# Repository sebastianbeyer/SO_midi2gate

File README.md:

Simple Midi to gate module with 12 gates. It's in the
[KOSMO format](https://www.lookmumnocomputer.com/modular)
made by Look Mum No Computer (20cm high, 7.5cm wide). Gates are 5V.

## How to get it

Download the [lates release](https://github.com/sebastianbeyer/SO_midi2gate/releases/latest)
including the gerber files and Arduino code

## Arduino code

The code can be found in the code directory and requires only a
[midi library](https://github.com/FortySevenEffects/arduino_midi_library).
Install instructions for this lib can be found
[in the repo](https://github.com/FortySevenEffects/arduino_midi_library#getting-started).

## Schematic

## BOM

| Reference| Quantity | Value | Description |
| -------- | -------- | ----- | ----------- |
| A1  | 1 |  Arduino Nano | |
| C1, C2, C5 |        3 | 10u   | EL cap      |
| C3, C4, C6, C7, C8, C9, C10, C11 | 8 |100n | ceramic disc cap |
| D1 | 1 | 1N4148 | diode |
| D2, D3, D4, D5, D6, D7, D8, D9, D10, D11, D12, D13 | 12 | LED | legs should be
25mm long|
| J1, J2 | 2 | MIDI jacks | |
| J1, J2 | 2 | Molex 3pin  | for MIDI jacks, you can also solder directly |
| J3, ... J15 |12 | Large jack sockets | |
| R1, R13, R14 | 3 | 220 | |
| R2, R3 | 2 | 10R | |
| R4, R5, R6, R7, R8, R9, R10, R11, R15, R16, R17, R18, R19, R20, R21, R22, R23, R24, R25, R26, R27, R28, R29, R30 | 24 |1k | |
| R12 | 1 | 10k |  |
| U1, U4, U5 | 3 | TL074 | opamp |
| U2 | 1 | 6N137 | optocoupler for midi |
| U3 | 1 | L7805 | 5V regulator |

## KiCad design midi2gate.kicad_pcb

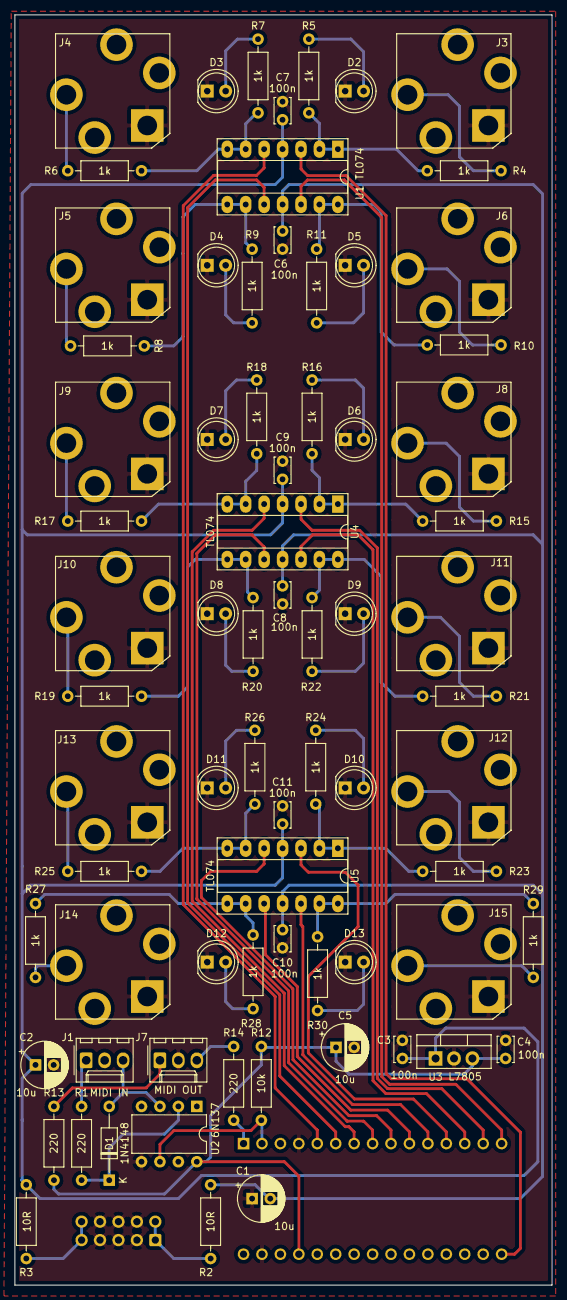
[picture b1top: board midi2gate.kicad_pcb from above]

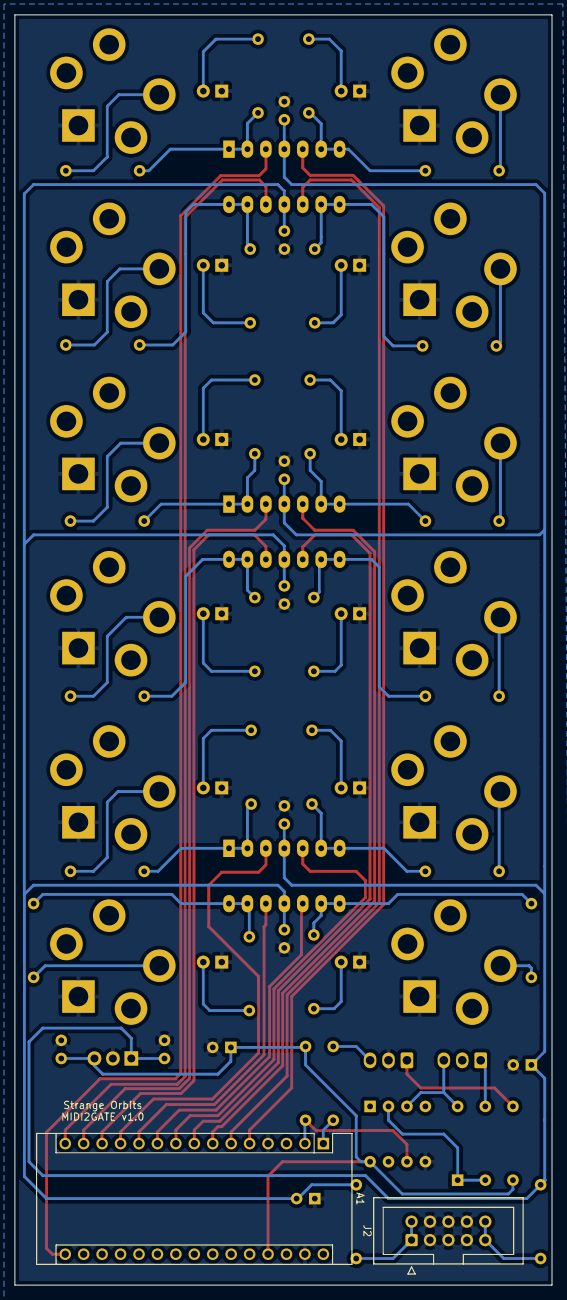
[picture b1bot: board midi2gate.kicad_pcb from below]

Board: 2 copper layers, 74.0 x 175.0 mm, 75 parts (2 on the bottom side), 61 nets.

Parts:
A1: Arduino_Nano_v3.x; Arduino_Nano
C1, C2, C5: 10u; CP_Radial_D6.3mm_P2.50mm
C3, C4, C6, C7, C8, C9, C10, C11: 100n; C_Disc_D3.4mm_W2.1mm_P2.50mm
D1: 1N4148; D_DO-35_SOD27_P10.16mm_Horizontal
D2, D3, D4, D5, D6, D7, D8, D9, D10, D11, D12, D13: LED; LED_D5.0mm
J1: MIDI IN; Molex_KK-254_AE-6410-03A_1x03_P2.54mm_Vertical
J2: Eurorack power; IDC-Header_2x05_P2.54mm_Vertical
J3: GATE1; Jack_6.35mm_PJ_629HAN
J4: GATE2; Jack_6.35mm_PJ_629HAN
J5: GATE3; Jack_6.35mm_PJ_629HAN
J6: GATE4; Jack_6.35mm_PJ_629HAN
J7: MIDI OUT; Molex_KK-254_AE-6410-03A_1x03_P2.54mm_Vertical
J8: GATE5; Jack_6.35mm_PJ_629HAN
J9: GATE6; Jack_6.35mm_PJ_629HAN
J10: GATE7; Jack_6.35mm_PJ_629HAN
J11: GATE8; Jack_6.35mm_PJ_629HAN
J12: GATE9; Jack_6.35mm_PJ_629HAN
J13: GATE10; Jack_6.35mm_PJ_629HAN
J14: GATE11; Jack_6.35mm_PJ_629HAN
J15: GATE12; Jack_6.35mm_PJ_629HAN
R1, R13, R14: 220; R_Axial_DIN0207_L6.3mm_D2.5mm_P7.62mm_Horizontal_silkvalue
R2, R3: 10R; R_Axial_DIN0207_L6.3mm_D2.5mm_P7.62mm_Horizontal_silkvalue
R4, R5, R6, R7, R8, R9, R10, R11, R15, R16, R17, R18, R19, R20, R21, R22, R23, R24, R25, R26, R27, R28, R29, R30: 1k; R_Axial_DIN0207_L6.3mm_D2.5mm_P7.62mm_Horizontal_silkvalue
R12: 10k; R_Axial_DIN0207_L6.3mm_D2.5mm_P7.62mm_Horizontal_silkvalue
U1, U4, U5: TL074; DIP-14_W7.62mm_Socket_LongPads
U2: 6N137; DIP-8_W7.62mm
U3: L7805; TO-220-3_Vertical

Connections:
+5V: A1.27, C4.1, C5.1, R12.1, R13.1, U2.8, U3.3
+12V: C2.1, C3.1, C7.2, C9.2, C11.2, R3.2, U1.4, U3.1, U4.4, U5.4
-12V: C1.2, C6.2, C8.2, C10.2, R2.2, U1.11, U4.11, U5.11
G1: A1.16, U1.3
G2: A1.5, U1.5
G3: A1.6, U1.10
G4: A1.15, U1.12
G5: A1.14, U4.3
G6: A1.7, U4.5
G7: A1.8, U4.10
G8: A1.13, U4.12
G9: A1.12, U5.3
G10: A1.9, U5.5
G11: A1.10, U5.10
G12: A1.11, U5.12
GND: A1.4, A1.29, C1.1, C2.2, C3.2, C4.2, C5.2, C6.1, C7.1, C8.1, C9.1, C10.1, C11.1, D2.1, D3.1, D4.1, D5.1, D6.1, D7.1, D8.1, D9.1, D10.1, D11.1, D12.1, D13.1, J2.3, J2.4, J2.5, J2.6, J2.7, J2.8, J3.S, J4.S, J5.S, J6.S, J7.2, J8.S, J9.S, J10.S, J11.S, J12.S, J13.S, J14.S, J15.S, U2.5, U3.2
MIDI_IN: A1.2, R12.2, U2.6
MIDI_OUT: A1.1, R14.1
unnamed: D1.1, R1.2, U2.2
unnamed: D1.2, J1.3, U2.3
unnamed: D2.2, R5.2
unnamed: D3.2, R7.2
unnamed: D4.2, R9.2
unnamed: D5.2, R11.2
unnamed: D6.2, R16.2
unnamed: D7.2, R18.2
unnamed: D8.2, R20.2
unnamed: D9.2, R22.2
unnamed: D10.2, R24.2
unnamed: D11.2, R26.2
unnamed: D12.2, R28.2
unnamed: D13.2, R30.2
unnamed: J1.1, R1.1
unnamed: J2.1, J2.2, R2.1
unnamed: J2.9, J2.10, R3.1
unnamed: J3.T, R4.2
unnamed: J4.T, R6.2
unnamed: J5.T, R8.2
unnamed: J6.T, R10.2
unnamed: J7.1, R13.2
unnamed: J7.3, R14.2
unnamed: J8.T, R15.2
unnamed: J9.T, R17.2
unnamed: J10.T, R19.2
unnamed: J11.T, R21.2
unnamed: J12.T, R23.2
unnamed: J13.T, R25.2
unnamed: J14.T, R27.2
unnamed: J15.T, R29.2
unnamed: R4.1, R5.1, U1.1, U1.2
unnamed: R6.1, R7.1, U1.6, U1.7
unnamed: R8.1, R9.1, U1.8, U1.9
unnamed: R10.1, R11.1, U1.13, U1.14
unnamed: R15.1, R16.1, U4.1, U4.2
unnamed: R17.1, R18.1, U4.6, U4.7
unnamed: R19.1, R20.1, U4.8, U4.9
unnamed: R21.1, R22.1, U4.13, U4.14
unnamed: R23.1, R24.1, U5.1, U5.2
unnamed: R25.1, R26.1, U5.6, U5.7
unnamed: R27.1, R28.1, U5.8, U5.9
unnamed: R29.1, R30.1, U5.13, U5.14

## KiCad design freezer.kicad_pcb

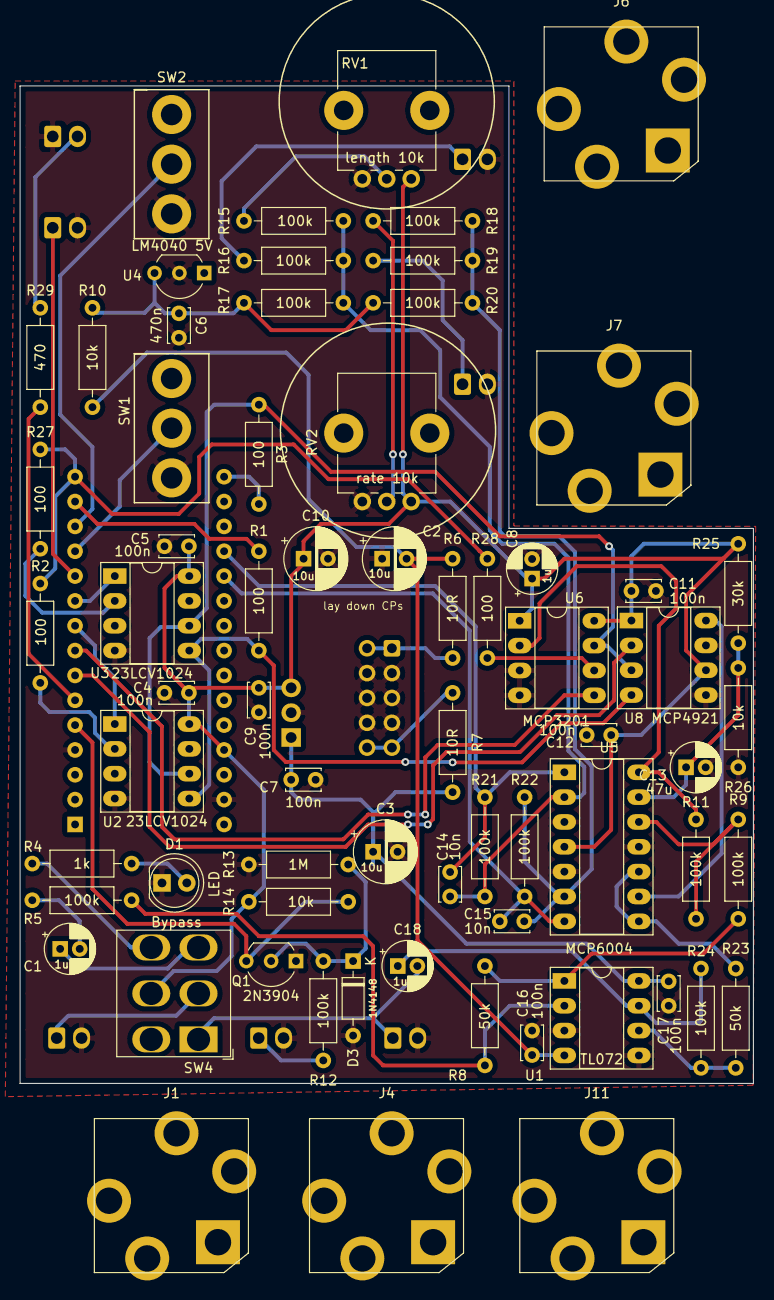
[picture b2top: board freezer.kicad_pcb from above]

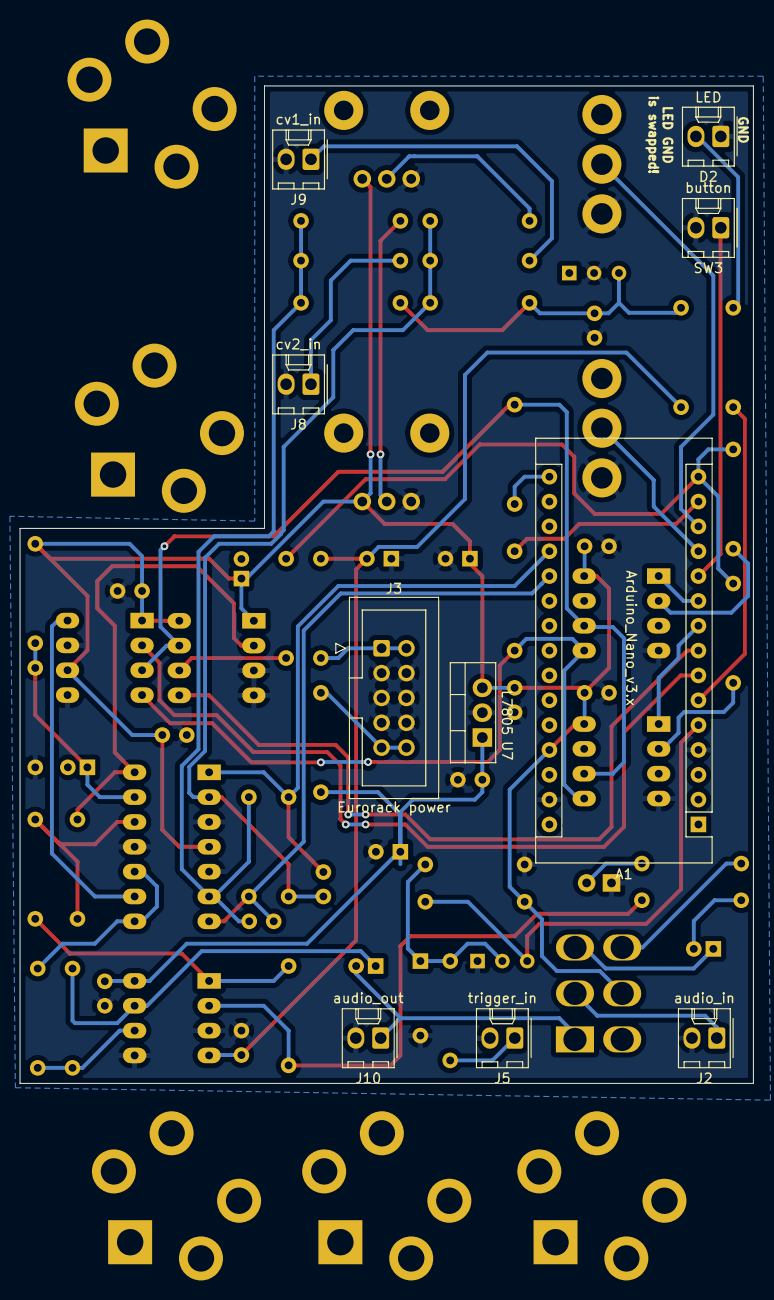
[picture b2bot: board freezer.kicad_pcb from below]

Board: 2 copper layers, 75.0 x 102.0 mm, 77 parts (10 on the bottom side), 50 nets.

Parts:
A1: Arduino_Nano_v3.x; Arduino_Nano
C1, C8, C18: 1u; CP_Radial_D5.0mm_P2.00mm
C2, C3, C10: 10u; CP_Radial_D6.3mm_P2.50mm
C4, C5, C7, C9, C11, C12, C16, C17: 100n; C_Disc_D3.4mm_W2.1mm_P2.50mm
C6: 470n; C_Disc_D3.4mm_W2.1mm_P2.50mm
C13: 47u; CP_Radial_D5.0mm_P2.00mm
C14, C15: 10n; C_Disc_D3.4mm_W2.1mm_P2.50mm
D1: LED; LED_D5.0mm
D2: LED; Molex_KK-254_AE-6410-02A_1x02_P2.54mm_Vertical
D3: 1N4148; D_DO-35_SOD27_P7.62mm_Horizontal
J1: audio in; Jack_6.35mm_PJ_629HAN
J2: audio_in; Molex_KK-254_AE-6410-02A_1x02_P2.54mm_Vertical
J3: Eurorack power; IDC-Header_2x05_P2.54mm_Vertical
J4: trigger in; Jack_6.35mm_PJ_629HAN
J5: trigger_in; Molex_KK-254_AE-6410-02A_1x02_P2.54mm_Vertical
J6: CV1 in; Jack_6.35mm_PJ_629HAN
J7: CV2 in; Jack_6.35mm_PJ_629HAN
J8: cv2_in; Molex_KK-254_AE-6410-02A_1x02_P2.54mm_Vertical
J9: cv1_in; Molex_KK-254_AE-6410-02A_1x02_P2.54mm_Vertical
J10: audio_out; Molex_KK-254_AE-6410-02A_1x02_P2.54mm_Vertical
J11: audio out; Jack_6.35mm_PJ_629HAN
Q1: 2N3904; TO-92_Inline_Wide
R1, R2, R3, R27, R28: 100; R_Axial_DIN0207_L6.3mm_D2.5mm_P7.62mm_Horizontal_silkvalue
R4: 1k; R_Axial_DIN0207_L6.3mm_D2.5mm_P7.62mm_Horizontal_silkvalue
R5, R9, R11, R12, R15, R16, R17, R18, R19, R20, R21, R22, R24: 100k; R_Axial_DIN0207_L6.3mm_D2.5mm_P7.62mm_Horizontal_silkvalue
R6, R7: 10R; R_Axial_DIN0207_L6.3mm_D2.5mm_P7.62mm_Horizontal_silkvalue
R8, R23: 50k; R_Axial_DIN0207_L6.3mm_D2.5mm_P7.62mm_Horizontal_silkvalue
R10, R14, R26: 10k; R_Axial_DIN0207_L6.3mm_D2.5mm_P7.62mm_Horizontal_silkvalue
R13: 1M; R_Axial_DIN0207_L6.3mm_D2.5mm_P7.62mm_Horizontal_silkvalue
R25: 30k; R_Axial_DIN0207_L6.3mm_D2.5mm_P7.62mm_Horizontal_silkvalue
R29: 470; R_Axial_DIN0207_L6.3mm_D2.5mm_P7.62mm_Horizontal_silkvalue
RV1: length 10k; Potentiometer_Alps_RK09K_Single_Vertical
RV2: rate 10k; Potentiometer_Alps_RK09K_Single_Vertical
SW1, SW2: SW_SPDT; SPDT SWITCH
SW3: button; Molex_KK-254_AE-6410-02A_1x02_P2.54mm_Vertical
SW4: Bypass; SW_CK_Lever_DPDT_72xx_CircularHoles
U1: TL072; DIP-8_W7.62mm_Socket_LongPads
U2, U3: 23LCV1024; DIP-8_W7.62mm_Socket_LongPads
U4: LM4040 5V; TO-92_Inline_Wide
U5: MCP6004; DIP-14_W7.62mm_Socket_LongPads
U6: MCP3201; DIP-8_W7.62mm_Socket_LongPads
U7: L7805; TO-220-3_Vertical
U8: MCP4921; DIP-8_W7.62mm_Socket_LongPads

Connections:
+5V: A1.27, C4.2, C5.2, C8.1, C9.1, C10.1, C11.1, C12.2, R14.1, R25.1, RV1.1, RV2.1, SW4.5, U2.8, U3.8, U5.4, U6.1, U6.8, U7.3, U8.1, U8.6
+12V: C3.1, C7.1, C17.2, R7.2, U1.8, U7.1
-12V: C2.2, C16.2, R6.2, R10.1, U1.4
AUDIO_IN: C1.1, SW4.3
AUDIO_OUT: C18.2, J10.1, SW4.1
BUTTON: A1.11, SW3.1
CIPO: A1.15, R2.1, R27.1, R28.2
COPI: R1.1, U2.5, U3.5, U8.4
CS_0: A1.8, U6.5
CS_1: A1.7, U8.2
CS_2: A1.9, U2.1
CS_3: A1.10, U3.1
CV1_IN: J9.1, R16.1
CV2_IN: J8.1, R19.1
CV_CH_1: A1.19, C14.1, R21.2, U5.1
CV_CH_2: A1.20, C15.1, R22.2, U5.7
GND: A1.4, A1.29, C2.1, C3.2, C4.1, C5.1, C6.2, C7.2, C8.2, C9.2, C10.2, C11.2, C12.1, C13.2, C16.1, C17.1, D1.1, D2.1, D3.2, J1.S, J2.2, J3.3, J3.4, J3.5, J3.6, J3.7, J3.8, J4.S, J5.2, J6.S, J7.S, J8.2, J9.2, J10.2, Q1.1, R13.2, R26.2, RV1.3, RV2.3, SW1.3, SW2.3, SW3.2, U1.3, U1.5, U2.4, U3.4, U4.2, U5.3, U5.5, U5.11, U6.3, U6.4, U7.2, U8.5, U8.7
IN_TRIGGER: A1.5, Q1.3, R14.2
LED_BUTTON: A1.6, R29.1
unnamed: A1.14, R1.2
unnamed: A1.16, R3.2
unnamed: C1.2, R5.1
unnamed: C13.1, R25.2, R26.1, U5.13
unnamed: C14.2, R15.2, R16.2, R17.2, R21.1, U5.2
unnamed: C15.2, R18.2, R19.2, R20.2, R22.1, U5.6
unnamed: C18.1, R24.2, U1.7
unnamed: D1.2, R4.2
unnamed: D2.2, R29.2
unnamed: D3.1, Q1.2, R12.2, R13.1
unnamed: J2.1, SW4.2
unnamed: J3.1, J3.2, R6.1
unnamed: J3.9, J3.10, R7.1
unnamed: R2.2, U2.2
unnamed: R4.1, SW4.6
unnamed: R5.2, R8.1, U1.2
unnamed: R8.2, R9.1, U1.1
unnamed: R9.2, R11.1, U5.12
unnamed: R11.2, U5.14, U6.2
unnamed: R15.1, RV1.2
unnamed: R18.1, RV2.2
unnamed: R23.1, U5.8, U5.10
unnamed: R23.2, R24.1, U1.6
unnamed: R27.2, U3.2
unnamed: R28.1, U6.6
unnamed: U5.9, U8.8
REF_-5V: C6.1, R10.2, R17.1, R20.1, U4.3
SCK: R3.1, U2.6, U3.6, U6.7, U8.3
SWITCH_1: A1.12, SW1.2
SWITCH_2: A1.13, SW2.2
TRIGGER_jack: J5.1, R12.1

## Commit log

2020-11-29 initial
2020-11-29 add libs and footprints
2020-11-29 add LTspice
2020-12-01 more work
2020-12-02 before moving the DAC ADC chips
2020-12-06 routing done!
2021-02-25 new trigger panel
2021-06-29 as sent to jlcpcb
2021-06-29 add gitignore
2021-06-29 add arduino code
2021-06-29 rename midi2trigger -> midi2gate
2021-06-29 Add readme
2021-06-29 add images
2021-06-29 wider images
2021-06-29 more readme
2021-06-29 fix schematic
2021-06-29 fix schematic2
2021-06-29 add BOM
2021-06-29 add arduino
2021-06-30 rearrange schematic like it is in the readme now
2021-06-30 add note about KOSMO format and 5V gates
2021-06-30 add note on LEDs
